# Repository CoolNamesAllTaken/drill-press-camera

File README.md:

# drill-press-camera
Hardware for a camera-guided drill press.

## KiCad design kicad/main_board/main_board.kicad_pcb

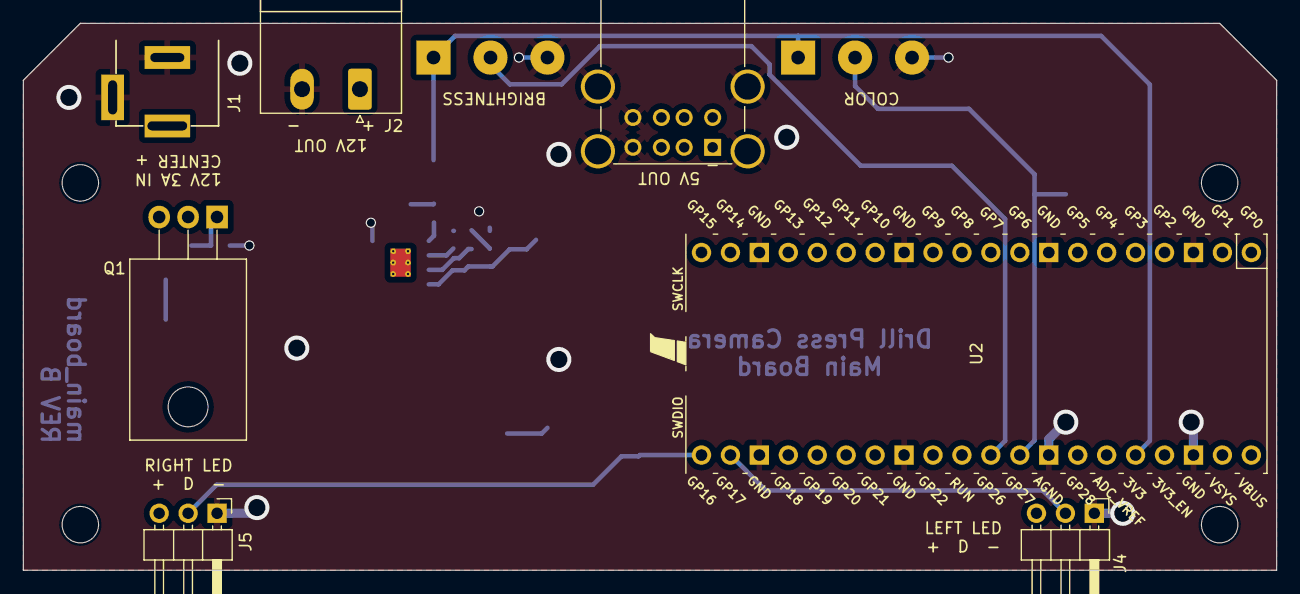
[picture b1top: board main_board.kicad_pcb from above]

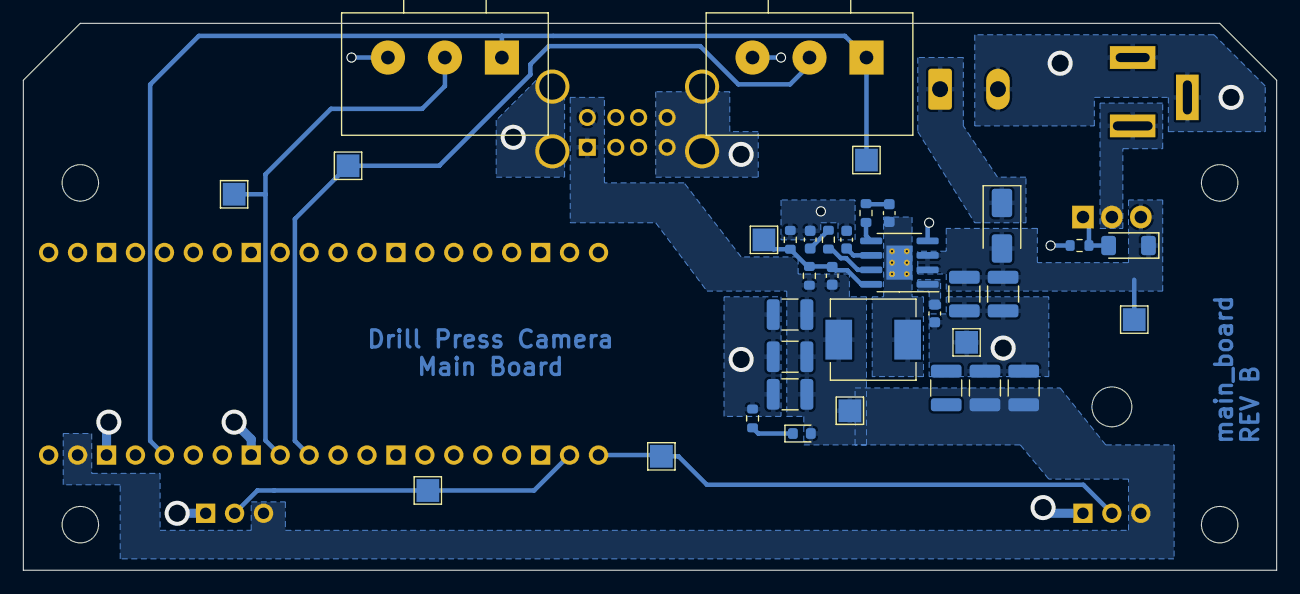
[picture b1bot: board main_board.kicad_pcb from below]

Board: 2 copper layers, 110.0 x 48.0 mm, 48 parts (36 on the bottom side), 20 nets.

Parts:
C1, C6, C7, C8, C9, C11, C12, C13: 22uF X7R 25V; C_1210_3225Metric
C2: 1nF; C_0603_1608Metric
C3: 33nF; C_0603_1608Metric
C4, C5: 0.1uF; C_0603_1608Metric
C10: DNP; C_0603_1608Metric
D1: 10V 0.5W; D_MiniMELF
D2: 40V 3A; D_SMA
D3: RED LED; LED_0603_1608Metric
GRAPHIC1: Graphic; bird_with_pants_small_flipped
H1, H2, H3, H4: MountingHole; MountingHole_3.2mm_M3
J1: Barrel_Jack; SOFNG_DC005-T20
J2: MSTBA 5.08mm 01x02; PhoenixContact_MSTBA_2,5_2-G-5,08_1x02_P5.08mm_Horizontal
J3: 61400826021; USB_A_Wuerth_61400826021_Horizontal_Stacked
J4, J5: 0.1" Male 01x03; PinHeader_1x03_P2.54mm_Horizontal
L1: 4.7uH 6A; L_Sunlord_MWSA0605S
PCB1: PCB; PCB_PN_REV
Q1: FQP27P06; TO-220-3_Horizontal_TabDown
R1: 10k; R_0603_1608Metric
R2: 110k 1%; R_0603_1608Metric
R3: 15k 1%; R_0603_1608Metric
R4: 0R; R_0603_1608Metric
R5: 2k; R_0603_1608Metric
R7: 300R; R_0603_1608Metric
RV1, RV2: 10k; Potentiometer_Alps_RK163_Single_Horizontal
TP1, TP3, TP4, TP5, TP6, TP7, TP9, TP10, TP11: TestPoint; TestPoint_Pad_2.0x2.0mm
U1: AOZ6605PI-1; SOIC-8-1EP_3.9x4.9mm_P1.27mm_EP2.29x3mm_ThermalVias
U2: Pico; RPi_Pico_TH_Socket

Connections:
+3V3: RV1.1, RV2.1, TP3.1, U2.36 (3V3)
+5V: C6.1, C8.1, C9.1, C10.1, C11.1, C12.1, C13.1, D3.2 (A), J3.1 (VBUS1), J3.5 (VBUS2), J4.3, J5.3, L1.2, R2.1, TP9.1, U2.39 (VSYS)
+12V: C1.1, C7.1, D1.1 (K), D2.2 (A), Q1.3 (S), TP11.1, U1.2 (EN), U1.3 (VIN)
/BRIGHTNESS_CTRL: RV1.2, TP7.1, U2.31 (GPIO26_ADC0)
/BUCK_FB: C10.2, R2.2, R3.1, TP10.1, U1.8 (FB)
/COLOR_CTRL: RV2.2, TP6.1, U2.32 (GPIO27_ADC1)
/LED_LEFT_DATA: J4.2, TP4.1, U2.22 (GPIO17)
/LED_RIGHT_DATA: J5.2, TP5.1, U2.21 (GPIO16)
GND: C1.2, C2.2, C3.2, C5.2, C6.2, C7.2, C8.2, C9.2, C11.2, C12.2, C13.2, J1.2, J2.2, J3.4 (GND1), J3.8 (GND2), J3.9 (Shield), J4.1, J5.1, R3.2, R5.2, R7.2, RV1.3, RV2.3, TP1.1, U1.4 (GND), U2.3 (GND), U2.8 (GND), U2.13 (GND), U2.18 (GND), U2.23 (GND), U2.28 (GND), U2.33 (AGND), U2.38 (GND)
unnamed: C2.1, R1.2
unnamed: C4.1, R4.2
unnamed: D1.2 (A), Q1.1 (G), R5.1
unnamed: D2.1 (K), J2.1
unnamed: D3.1 (K), R7.1
unnamed: J1.1, Q1.2 (D)
unnamed: R4.1, U1.5 (BST)
unnamed: R1.1, U1.7 (COMP)
unnamed: C4.2, L1.1, U1.9 (LX)
unnamed: C3.1, U1.1 (SS)
unnamed: C5.1, U1.6 (VCC)

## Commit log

2023-05-23 Microscope box without PCB stuff
2023-06-14 Begin designing PCB
2023-06-20 First working version
2023-06-20 Add additional files
2023-06-20 Add images and README
